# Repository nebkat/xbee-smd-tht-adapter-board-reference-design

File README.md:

# Digi XBee® SX 868 SMD -> THT Adapter Board

This repository contains KiCAD schematics and the PCB design for a through hole adapter board for the Digi XBee® SX 868.

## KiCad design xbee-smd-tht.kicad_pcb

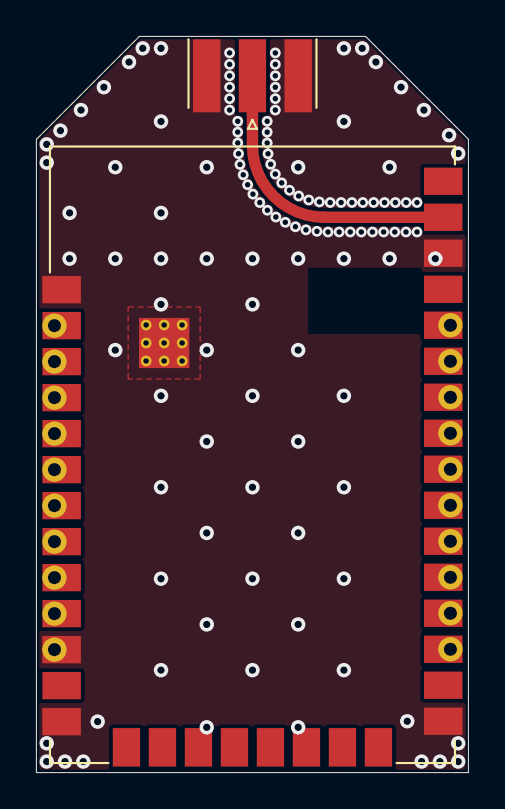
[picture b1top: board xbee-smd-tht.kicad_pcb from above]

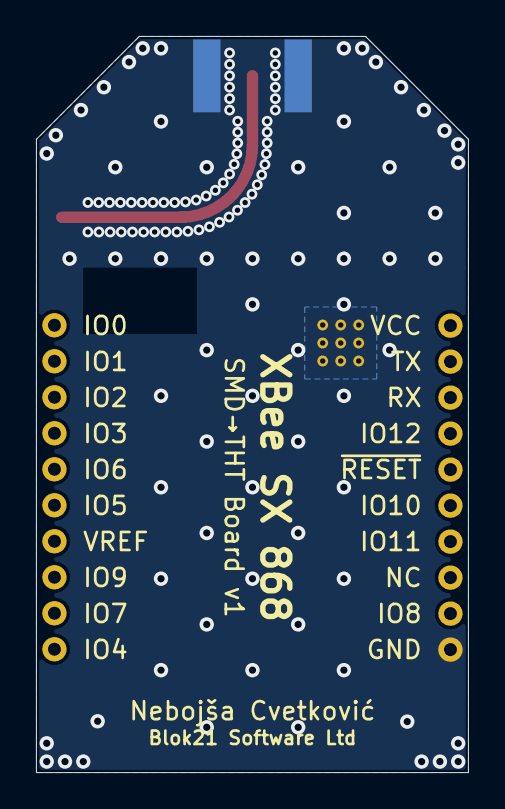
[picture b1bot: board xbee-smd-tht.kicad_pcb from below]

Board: 2 copper layers, 24.0 x 40.9 mm, 4 parts (2 on the bottom side), 20 nets.

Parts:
J1: Conn_Coaxial; SMA_Linx_CONSMA003.062_EdgeMount
J2, J3: Conn_01x10; PinHeader_1x10_P2.00mm_Vertical
U1: XBee_SMT; Digi_XBee_SMT_GND_Pad

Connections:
DIN: J2.3, U1.4
DIO0: J3.1, U1.33
DIO1: J3.2, U1.32
DIO2: J3.3, U1.31
DIO3: J3.4, U1.30
DIO4: J3.10, U1.24
DIO5: J3.6, U1.28
DIO6: J3.5, U1.29
DIO7: J3.9, U1.25
DIO8: J2.9, U1.10
DIO9: J3.8, U1.26
DIO10: J2.6, U1.7
DIO11: J2.7, U1.8
DIO12: J2.4, U1.5
DOUT: J2.2, U1.3
GND: J1.2, J2.10, U1.1, U1.11, U1.13, U1.22, U1.35, U1.38
unnamed: J1.1, U1.36
RESET: J2.5, U1.6
VCC: J2.1, U1.2
VREF: J3.7, U1.27
